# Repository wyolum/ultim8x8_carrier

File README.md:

# ULTiM8x8 3x3 carrier board

A 208 x 208 mm, 2-layer backplane that holds nine [ULTiM8x8](https://github.com/wyolum/ultim8x8) APA102 tiles in a 3 x 3 grid (576 LEDs). The tiles bolt to it on M3 standoffs, and the standoffs carry 5 V, GND, clock and data. A Raspberry Pi Pico 2 W plugs into the back and drives the first tile directly.

**Status: draft for review, simplified 2026-11-22. Not fabricated. Please do not order from this yet.**

Anool, this README is meant to be everything you need. There are six things to check, each with a picture: the [review checklist](#review-checklist).

## Read this first

1. **The board came first, not a schematic.** A Python script, `2026-11-21_build_carrier.py`, places every pad and track and assigns the nets. The [schematic](docs/2026-11-22_schematic.pdf) is drawn afterwards from the saved board, so it always agrees with the board and cannot catch a wrong net. KiCad's DRC passes with 0 violations and 0 unconnected pads ([report](docs/2026-11-22_drc_report.txt)), which proves the copper matches the nets the script assigned, not that those nets are right.
2. **The script and this README were written by an AI assistant (Claude) working with Justin.** "I" below is the assistant. Nobody who knows KiCad well has looked at the result.
3. **The .kicad_pcb is generated output.** Edits made in KiCad are overwritten the next time the script runs. If you would rather fix things by hand, say so and the script gets retired.

An earlier version of this repo also had an Arduino UNO header, an AlaMode header, a level shifter and a clock/data bus between them. All of that is gone. It is in the git history if it is ever wanted.

## The whole circuit

| Net | Connects |
|---|---|
| `VIN` | J2 pin 2, F1 pin 1 |
| `+5V` | F1 pin 2, D4 cathode, C1 +, D1 anode, every tile 5V hole. B.Cu pour. |
| `GND` | J2 pin 1, D4 anode, C1 -, Pico pins 3, 8, 13, 18, 23, 28, 38, every tile GND hole. F.Cu pour. |
| `VSYS` | D1 cathode, Pico pin 39 |
| `CLK0` | Pico pin 31 (GP26, SPI1 SCK), tile T0 clock in |
| `DAT0` | Pico pin 32 (GP27, SPI1 TX), tile T0 data in |
| `CLK1` to `CLK8`, `DAT1` to `DAT8` | Tile n-1 out to tile n in |
| `CLK9`, `DAT9` | T8 outputs, unconnected |

The Pico drives the first tile at 3.3 V with no level shifter. Each diamond header pin is on the same net as the matching tile terminal.

| Ref | Part | Footprint | LCSC |
|---|---|---|---|
| J2 | 2-pin screw terminal, 5.08 mm, Phoenix 1715721 | Phoenix MKDS 1,5/2-5.08 | C480516 |
| F1 | Mini blade fuse holder, Keystone 3568, with a 3 A mini blade fuse | library, holes opened to 2.0 mm | C5249699, out of stock 2026-11-22; XFCN XF-508P-B-B (C19727305) should also fit |
| D4 | 5 A Schottky, SS54 | SMC | C330398 |
| C1 | 1000 uF 10 V electrolytic, 10 mm diameter, 13 mm tall | Radial D10 P5 | C55565640 |
| D1 | 1 A Schottky, 1N5819W | SOD-123 | C727115 |
| A1 | Pico 2 W on two 1x20 sockets, 8.5 mm tall | drawn in script | C22373906, qty 2 |
| T0 to T8 | Tile terminals, 8 plated M3 holes each | drawn in script | none |
| T*n*In1, In2, Out1, Out2 | 2x2 pin header pads turned 45 degrees, for v2 tiles. **Do not populate.** | drawn in script | none |

## How the pictures are oriented

- **LED-side view** means looking at the finished box from the front, through the tiles. The front copper (F.Cu) faces the tiles.
- **Back view** means the board as you hold it to solder the parts. It is the LED-side view mirrored left to right.
- In the color pictures the pours are hidden so the traces show: **red is F.Cu, blue is B.Cu**.
- Coordinates are millimeters from the board center, x right and y up in the LED-side view.

*Back view. Supply parts at center, Pico at right, both below the middle. Signal enters at tile T0 (lower right here), runs along the bottom row, back along the middle row, then along the top row. The middle row of tiles is mounted turned 180 degrees so the hops between rows stay short.*

## Review checklist

### 1. Tile terminal holes and nets

The tiles Justin has are an older revision with 8 terminal holes: an outer square at +/-22.86 mm (5V on the two top corners, GND on the two bottom) and an inner square at +/-7.62 mm (clock in, clock out, data in, data out). The v2 layout in the ultim8x8 repo has 16 holes; these 8 are a subset with the same nets, so the board should fit both.

*The tile in hand, seen from the back. Flip it left to right to compare with the LED-side pictures.*

*Every tile pad read back from the saved board, LED-side view. Arrows join a tile's outputs to the next tile's inputs.*

Please check:
- Hole positions and nets against a real tile or the tile layout. A first, 3D-printed version of this backplane was scrapped because it was routed for the 16-hole tile.
- Pad size: 3.2 mm hole, 7.0 mm pad on both sides, to seat a 5.5 mm hex standoff on the front and a screw head on the back.
- Whether a plated M3 hole with a standoff and screw is a sound way to carry up to about 3.8 A per tile at full white.

### 2. Power pours

*F.Cu, filled, LED-side view: GND pour plus the clock and data traces.*

*B.Cu, filled, seen through from the LED side: +5V pour.*

Please check:
- **Pour pullback.** Both pours stop 1 mm inside the 184 mm frame opening, leaving 13 mm of bare board around the edge. The frame wall and the eight perimeter screws sit there, and the corner screws run through to metal standoffs at the front of the box.
- **Solid pad connections.** Tile power pads, J2 and F1 connect to the pours without thermal spokes, since they carry current and the tile pads are never soldered. Other soldered pads use spokes 0.6 mm wide with a 0.4 mm gap.
- Pour clearance is 0.4 mm. The eight perimeter holes are unplated, 3.2 mm.

### 3. Tile-to-tile signal traces

*Front, LED-side view, right-hand side: the hop from the bottom row up to the middle row.*

Clock and data run on F.Cu, 0.5 mm wide. Along a row each hop is a straight 45.7 mm trace. At a row turn both hops share one column of holes, so the longer one steps 4.27 mm outward around the other's pads, in the 1.5 mm gap between the tile pads and the inner pin of the diamond headers.

Please check:
- Whether 0.5 mm traces across a ground pour are reasonable for APA102 clock and data, and whether you would add series resistors.
- The stepped trace runs about 0.6 mm from the tile pads on one side and the diamond pins on the other.

### 4. Supply entry, fuse and reverse-polarity diode

*Back view. J2 pin 1 (square) is GND, the other is the supply. C1's square pad is +. The wide trace from J2 to F1 is on both layers.*

The supply goes J2 to F1 to the +5V pour. D4 sits across the supply after the fuse, cathode on +5V, so a reversed supply forward-biases it and blows the fuse. These parts sit in a square between tiles T1 and T4 that has no tile pad, screw head or diamond header.

Please check:
- J2 and C1 polarity.
- The J2 to F1 trace: 3 mm wide on both layers, about 12 mm long. Full white on 576 LEDs is nominally 34 A, which this entry cannot carry; the box runs far below that, limited in firmware. The chosen setting, a warm white (R 255, G 190, B 120) at global brightness 1/31, works out to about 155 mA per tile (calculated from 20 mA per color at full scale, not measured), so about 1.4 A for nine tiles.
- D4 as a crowbar. It has to survive long enough to blow whatever fuse is fitted. Four 0.4 mm vias take its anode to the ground pour.
- Fuse rating: 3 A, about twice the 1.4 A running current. Please say if the J2 to F1 trace or D4 looks wrong for that.

### 5. Pico 2 W

*Back view. USB end of the Pico is at the right, pin 1 at the square pad. Tile T0's four signal terminals and two of its diamond headers are below.*

Clock is GP26 (pin 31) and data is GP27 (pin 32), the hardware SPI1 pair. They were chosen because they are the two Pico pins nearest T0's inputs: the clock trace drops 4 mm straight into the clock terminal, and the data trace steps around that pad and runs 20 mm down to the data terminal. Both are 0.5 mm on B.Cu.

Please check:
- **Pico pin numbering and orientation.** The Pico's top faces away from the board. Pins 1 to 20 are the upper row in this picture, from the USB end; pins 40 down to 21 are the lower row, from the USB end.
- **D1 direction:** anode on +5V, cathode on VSYS (pin 39), so a USB cable cannot power the LED rail.
- **3.3 V drive.** No level shifter. A 5 V APA102 nominally wants 3.5 V for a high, so this is 0.2 V under spec on paper. Breadboard test, 2026-11-22: one tile at 5 V driven straight from a Pico 2 W on these two pins, hardware SPI1 at 1 MHz, frames resent 20 times a second, showed clean steady color. That is one tile on one bench, not a guarantee for every tile. Only the first LED of T0 sees the 3.3 V signal; every LED after it gets a regenerated 5 V signal.
- Mechanical: the Pico sits over two tile screw heads, which is why it goes on sockets and is not soldered flat.

### 6. Diamond headers for v2 tiles

**These are not populated.** The pads stay on the board, but no headers are fitted or ordered.

*Front, LED-side view of tile T1. The small pads along the top edge belong to the supply parts on the back.*

The v2 tile has four 2x2 pin headers turned 45 degrees, 15.24 mm from the tile center. The carrier has matching pads so a v2 tile can connect through pin headers as well as through its standoffs. Positions and pin roles were read from `ultim_8x8_v2/ultim8x8.kicad_pcb`, LED-side view, tile not turned:

| Header | Center (mm) | Inner pin | Outer pin | Other two |
|---|---|---|---|---|
| In1 | (-15.24, 0) | clock in | GND | 5V above, data in below |
| Out2 | (+15.24, 0) | clock out | GND | 5V above, data out below |
| Out1 | (0, +15.24) | clock out | GND | 5V left, data out right |
| In2 | (0, -15.24) | clock in | GND | 5V left, data in right |

35 of the 36 are placed. T0 Out1 is left out because the Pico's pin row crosses it; T0 still has In1, In2 and Out2. Clock pins route to the tile's clock terminal on F.Cu and data pins to the data terminal on B.Cu.

Please check:
- **The pin roles.** I worked them out from the pad positions and the 45 degree footprint rotations in the v2 file. A sign error in that rotation would swap pins. The result is at least self-consistent: facing headers on neighboring tiles line up 5V to 5V and data to data.
- **Stack height.** The tiles sit on 10 mm standoffs. A standard pin header and socket stack to about 11 mm.
- Whether these are worth having on a board whose standoffs already carry every signal. They are the most intricate routing on the board and are easy to remove.

## Assembly notes

- **No washers on the tile screws or standoffs.** Each tile pad is 7.0 mm across and the opposite rail's pour starts 0.4 mm beyond it, so anything wider than about 7.8 mm sits over the other rail with only solder mask between. M3 pan heads (about 5.5 to 6 mm) and 5.5 mm hex standoffs (6.35 mm across corners) stay inside the pad.
- **Check polarity at J2 with a meter before fitting the tiles.** J2 pin 1 (square pad) is GND. Polarity can only go wrong where the barrel jack is wired to J2.
- **Use a supply rated 5 A or less.** D4 is a 5 A part. With a reversed supply inside that limit it holds the rail at about -0.5 V whether or not the 3 A fuse opens. A larger supply can overheat D4 before the fuse blows.

## Schematic and fab files

The [schematic](docs/2026-11-22_schematic.pdf) ([image](docs/2026-11-22_schematic.png)) has no wires: every pin carries a label, and pins with the same label are on the same net. I exported its netlist with `kicad-cli` and compared it with the board pin by pin: 232 connected pins, 24 nets, no differences. Opening it in KiCad gives one library warning per symbol, because the symbols exist only inside the sheet.

`fab/` has Gerbers and drill files (also zipped), a BOM, a position file and an IPC-D-356 netlist, so you can look at the board in a Gerber viewer. The "do not order" at the top still stands.

## Files

| File | What it is |
|---|---|
| `ultim_carrier.kicad_pcb`, `.kicad_pro`, `.kicad_sch` | Board (pours filled), project and schematic, KiCad 10.0.3 |
| `2026-11-21_build_carrier.py` | Board generator. All dimensions and nets are near the top. |
| `2026-11-21_build_schematic.py` | Draws the schematic from the saved board |
| `2026-11-21_export_fab.py` | Writes everything in `fab/` |
| `2026-11-21_plot_carrier.py`, `2026-11-21_render_docs.py` | Draw the pictures in `docs/` |

To rebuild from scratch on macOS with KiCad 10:

```bash
KP=/Applications/KiCad/KiCad.app/Contents/Frameworks/Python.framework/Versions/Current/bin/python3
KC=/Applications/KiCad/KiCad.app/Contents/MacOS/kicad-cli
$KP 2026-11-21_build_carrier.py ultim_carrier.kicad_pcb pads.json
$KC pcb drc --refill-zones --save-board --severity-all -o docs/2026-11-22_drc_report.txt ultim_carrier.kicad_pcb
python3 2026-11-21_plot_carrier.py pads.json docs/2026-11-22_tile_nets.png
python3 2026-11-21_render_docs.py
python3 2026-11-21_build_schematic.py pads.json ultim_carrier.kicad_sch
$KC sch export pdf -o docs/2026-11-22_schematic.pdf ultim_carrier.kicad_sch
python3 2026-11-21_export_fab.py
```

The script saves the pours unfilled, because filling zones from KiCad 10's Python crashes without a GUI. The `drc --refill-zones --save-board` step fills them.

## Things that are not done

- The schematic is derived from the board. Nobody has drawn the circuit independently.
- The Gerbers have not been through a fab's checker.
- The enclosure is being redesigned around this board and has not been checked against it in 3D.

## License

[CERN Open Hardware Licence v1.2](LICENSE), the same licence as [ULTiM8x8](https://github.com/wyolum/ultim8x8).

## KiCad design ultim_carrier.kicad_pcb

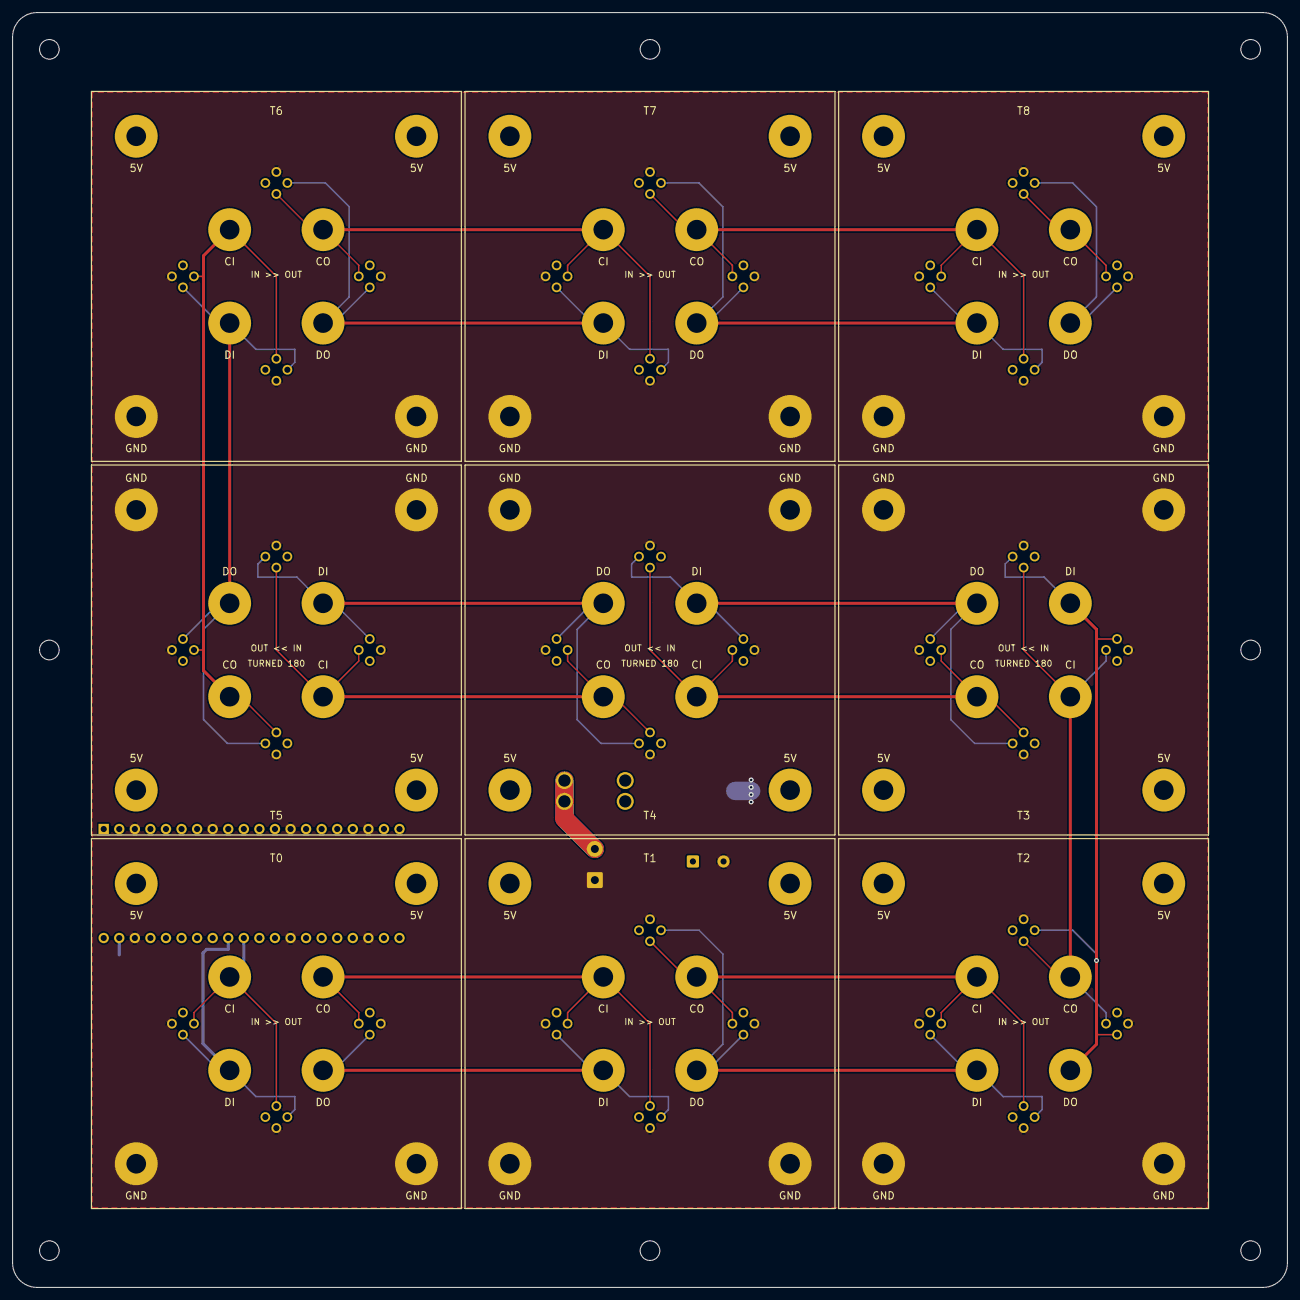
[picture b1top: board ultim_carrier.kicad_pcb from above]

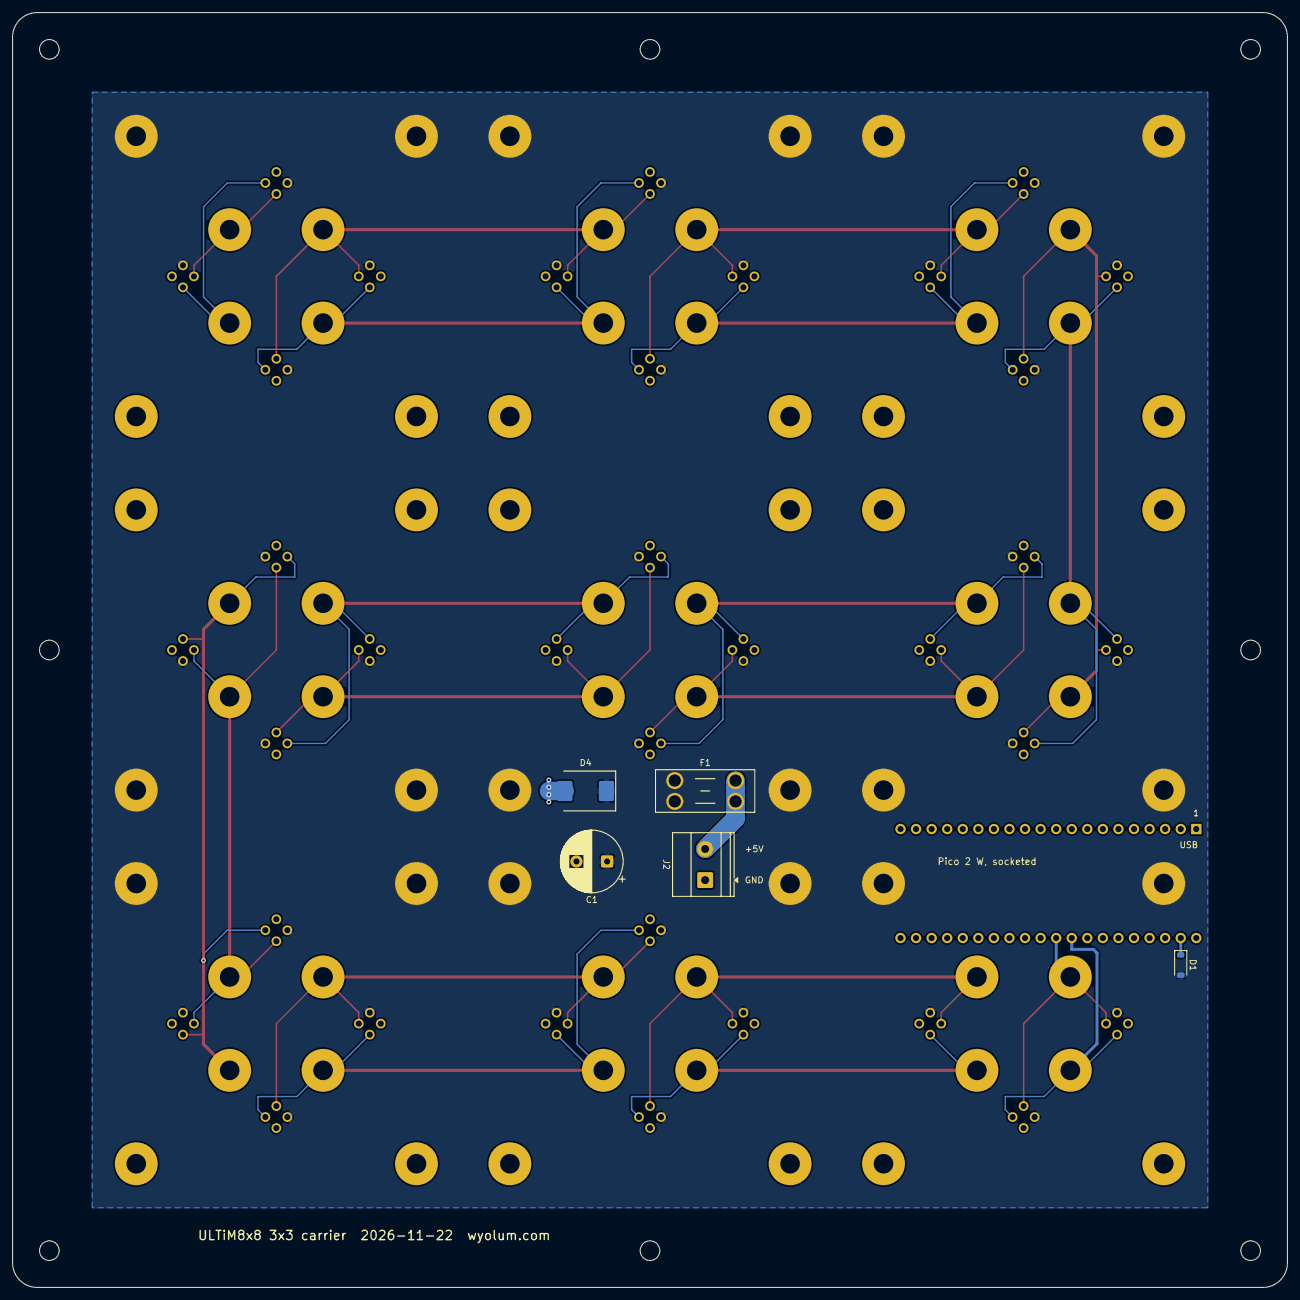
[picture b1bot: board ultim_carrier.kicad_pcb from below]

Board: 2 copper layers, 208.0 x 208.0 mm, 58 parts (5 on the bottom side), 24 nets.

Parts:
A1: Pico 2 W on 1x20 sockets
C1: 1000u 10V; CP_Radial_D10.0mm_P5.00mm
D1: MBR120 / 1N5819W; D_SOD-123
D4: SS54 or S5B; D_SMC
F1: mini blade holder, 3 A fuse; Fuseholder_Blade_Mini_Keystone_3568
H0, H1, H2, H3, H4, H5, H6, H7: M3
J2: 5V in; TerminalBlock_Phoenix_MKDS-1,5-2-5.08_1x02_P5.08mm_Horizont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
T0, T1, T2, T3, T4, T5, T6, T7, T8: ULTiM8x8
T0In1, T0In2, T0Out2, T1In1, T1In2, T1Out1, T1Out2, T2In1, T2In2, T2Out1, T2Out2, T3In1, T3In2, T3Out1, T3Out2, T4In1, T4In2, T4Out1, T4Out2, T5In1, T5In2, T5Out1, T5Out2, T6In1, T6In2, T6Out1, T6Out2, T7In1, T7In2, T7Out1, T7Out2, T8In1, T8In2, T8Out1, T8Out2: 2x2 diamond

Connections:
+5V: C1.1, D1.2, D4.1, F1.2, T0.5VA, T0.5VB, T0In1.5V, T0In2.5V, T0Out2.5V, T1.5VA, T1.5VB, T1In1.5V, T1In2.5V, T1Out1.5V, T1Out2.5V, T2.5VA, T2.5VB, T2In1.5V, T2In2.5V, T2Out1.5V, T2Out2.5V, T3.5VA, T3.5VB, T3In1.5V, T3In2.5V, T3Out1.5V, T3Out2.5V, T4.5VA, T4.5VB, T4In1.5V, T4In2.5V, T4Out1.5V, T4Out2.5V, T5.5VA, T5.5VB, T5In1.5V, T5In2.5V, T5Out1.5V, T5Out2.5V, T6.5VA, T6.5VB, T6In1.5V, T6In2.5V, T6Out1.5V, T6Out2.5V, T7.5VA, T7.5VB, T7In1.5V, T7In2.5V, T7Out1.5V, T7Out2.5V, T8.5VA, T8.5VB, T8In1.5V, T8In2.5V, T8Out1.5V, T8Out2.5V
CLK0: A1.31, T0.CI, T0In1.CI, T0In2.CI
CLK1: T0.CO, T0Out2.CO, T1.CI, T1In1.CI, T1In2.CI
CLK2: T1.CO, T1Out1.CO, T1Out2.CO, T2.CI, T2In1.CI, T2In2.CI
CLK3: T2.CO, T2Out1.CO, T2Out2.CO, T3.CI, T3In1.CI, T3In2.CI
CLK4: T3.CO, T3Out1.CO, T3Out2.CO, T4.CI, T4In1.CI, T4In2.CI
CLK5: T4.CO, T4Out1.CO, T4Out2.CO, T5.CI, T5In1.CI, T5In2.CI
CLK6: T5.CO, T5Out1.CO, T5Out2.CO, T6.CI, T6In1.CI, T6In2.CI
CLK7: T6.CO, T6Out1.CO, T6Out2.CO, T7.CI, T7In1.CI, T7In2.CI
CLK8: T7.CO, T7Out1.CO, T7Out2.CO, T8.CI, T8In1.CI, T8In2.CI
CLK9: T8.CO, T8Out1.CO, T8Out2.CO
DAT0: A1.32, T0.DI, T0In1.DI, T0In2.DI
DAT1: T0.DO, T0Out2.DO, T1.DI, T1In1.DI, T1In2.DI
DAT2: T1.DO, T1Out1.DO, T1Out2.DO, T2.DI, T2In1.DI, T2In2.DI
DAT3: T2.DO, T2Out1.DO, T2Out2.DO, T3.DI, T3In1.DI, T3In2.DI
DAT4: T3.DO, T3Out1.DO, T3Out2.DO, T4.DI, T4In1.DI, T4In2.DI
DAT5: T4.DO, T4Out1.DO, T4Out2.DO, T5.DI, T5In1.DI, T5In2.DI
DAT6: T5.DO, T5Out1.DO, T5Out2.DO, T6.DI, T6In1.DI, T6In2.DI
DAT7: T6.DO, T6Out1.DO, T6Out2.DO, T7.DI, T7In1.DI, T7In2.DI
DAT8: T7.DO, T7Out1.DO, T7Out2.DO, T8.DI, T8In1.DI, T8In2.DI
DAT9: T8.DO, T8Out1.DO, T8Out2.DO
GND: A1.3, A1.8, A1.13, A1.18, A1.23, A1.28, A1.38, C1.2, D4.2, J2.1, T0.GNDA, T0.GNDB, T0In1.GND, T0In2.GND, T0Out2.GND, T1.GNDA, T1.GNDB, T1In1.GND, T1In2.GND, T1Out1.GND, T1Out2.GND, T2.GNDA, T2.GNDB, T2In1.GND, T2In2.GND, T2Out1.GND, T2Out2.GND, T3.GNDA, T3.GNDB, T3In1.GND, T3In2.GND, T3Out1.GND, T3Out2.GND, T4.GNDA, T4.GNDB, T4In1.GND, T4In2.GND, T4Out1.GND, T4Out2.GND, T5.GNDA, T5.GNDB, T5In1.GND, T5In2.GND, T5Out1.GND, T5Out2.GND, T6.GNDA, T6.GNDB, T6In1.GND, T6In2.GND, T6Out1.GND, T6Out2.GND, T7.GNDA, T7.GNDB, T7In1.GND, T7In2.GND, T7Out1.GND, T7Out2.GND, T8.GNDA, T8.GNDB, T8In1.GND, T8In2.GND, T8Out1.GND, T8Out2.GND
VIN: F1.1, J2.2
VSYS: A1.39, D1.1

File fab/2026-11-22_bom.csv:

group,qty,references,value,footprint,part to buy,LCSC,buy qty,note
always fitted,1,A1,Pico 2 W on 1x20 sockets,drawn in the build script,"Hong Cheng HC-PM254-8.5H-1x20PZ, 1x20 socket, 8.5 mm tall",C22373906,2,two sockets for one Pico 2 W; the Pico itself is not on this list
always fitted,1,C1,1000u 10V,CP_Radial_D10.0mm_P5.00mm,Econd 1000uF10V10x13GF,C55565640,1,"10 mm diameter, 13 mm tall, 5 mm lead pitch"
always fitted,1,D1,MBR120 / 1N5819W,D_SOD-123,TWGMC 1N5819W,C727115,1,40 V 1 A Schottky
always fitted,1,D4,SS54 or S5B,D_SMC,LGE SS54,C330398,1,40 V 5 A Schottky
always fitted,1,F1,"mini blade holder, 3 A fuse",Fuseholder_Blade_Mini_Keystone_3568,Keystone 3568,C5249699,1,"LCSC stock was 0 on 2026-11-22. Possible substitute XFCN XF-508P-B-B (C19727305): pins 9.80 x 3.40 mm against this footprint's 9.92 x 3.40 mm, which the holes, opened to 2.0 mm, allow for; not tried"
always fitted,1,in F1,3 A mini blade fuse,,any 3 A mini (ATM) blade fuse,,1,no LCSC number chosen
always fitted,1,J2,5V in,"TerminalBlock_Phoenix_MKDS-1,5-2-5.08_1x02_P5.08mm_Horizontal","Phoenix Contact 1715721 (MKDS 1,5/2-5,08)",C480516,1,
do not populate,35,T0In1 ... T8Out2 (35 headers),2x2 diamond,drawn in the build script,,,0,"pads for v2 tile headers, left empty"

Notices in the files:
ultim_carrier.kicad_pcb:
CERN OHL v1.2. Generated by 2026-11-21_build_carrier.py
